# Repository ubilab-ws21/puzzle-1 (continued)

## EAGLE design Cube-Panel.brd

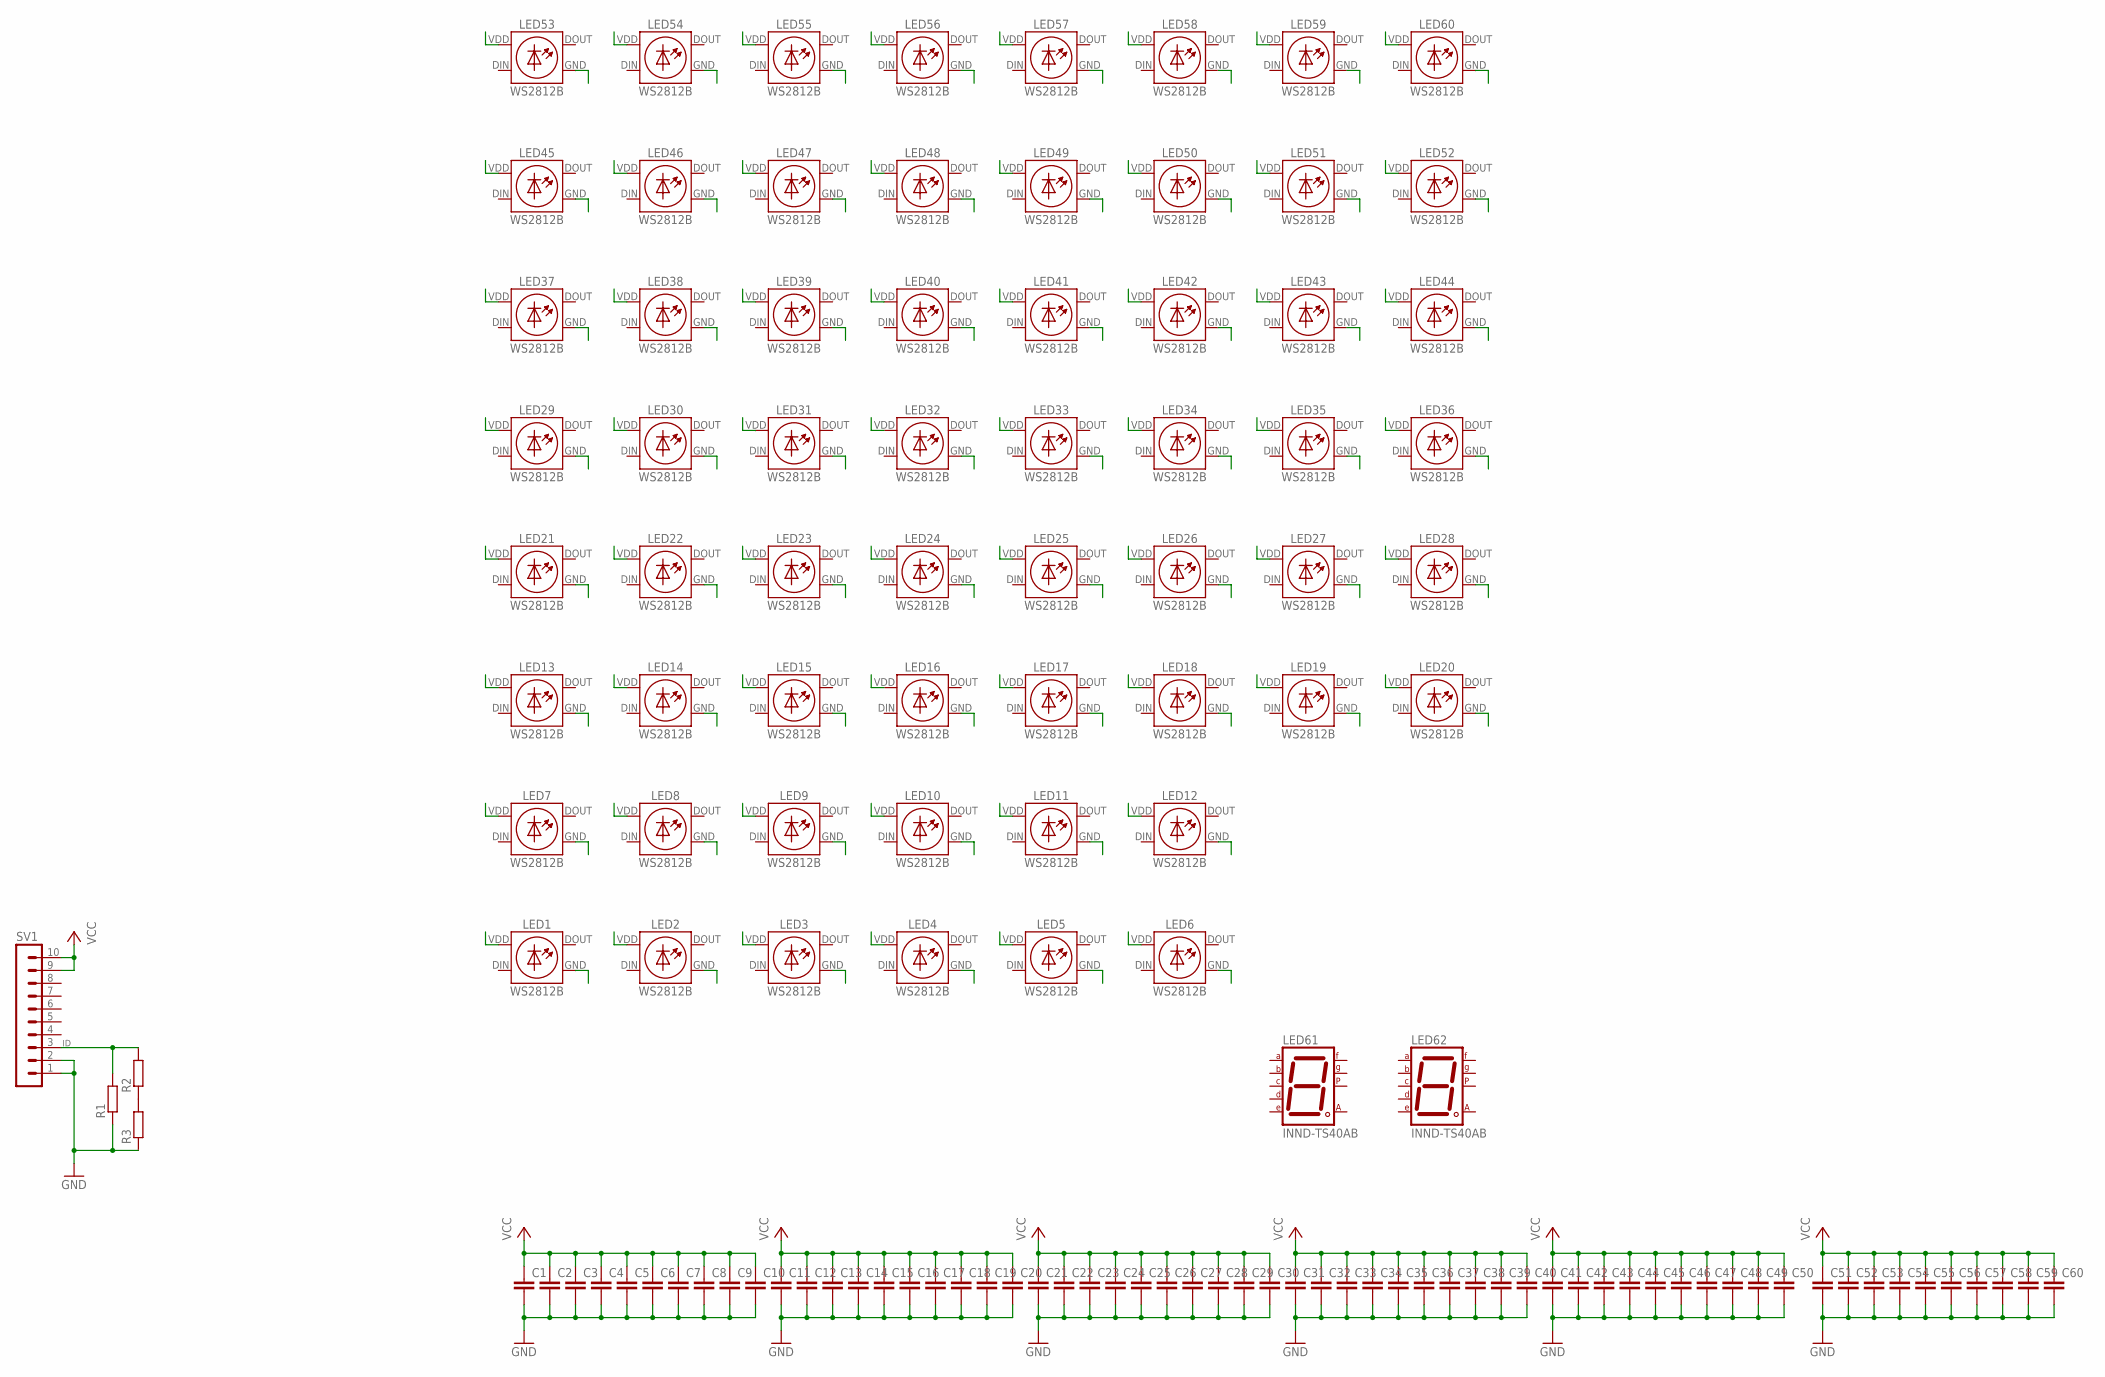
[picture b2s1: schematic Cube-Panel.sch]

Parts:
C1, C2, C3, C4, C5, C6, C7, C8, C9, C10, C11, C12, C13, C14, C15, C16, C17, C18, C19, C20, C21, C22, C23, C24, C25, C26, C27, C28, C29, C30, C31, C32, C33, C34, C35, C36, C37, C38, C39, C40, C41, C42, C43, C44, C45, C46, C47, C48, C49, C50, C51, C52, C53, C54, C55, C56, C57, C58, C59, C60: KONDENSATOR-0603; 0603
LED1, LED2, LED3, LED4, LED5, LED6, LED7, LED8, LED9, LED10, LED11, LED12, LED13, LED14, LED15, LED16, LED17, LED18, LED19, LED20, LED21, LED22, LED23, LED24, LED25, LED26, LED27, LED28, LED29, LED30, LED31, LED32, LED33, LED34, LED35, LED36, LED37, LED38, LED39, LED40, LED41, LED42, LED43, LED44, LED45, LED46, LED47, LED48, LED49, LED50, LED51, LED52, LED53, LED54, LED55, LED56, LED57, LED58, LED59, LED60: WS2812B
LED61, LED62: INND-TS40AB; 7SEG-13
R1, R2, R3: WIDERSTAND_0603; R0603
SV1: MA10-1

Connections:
GND: C1.P$2 (2), C2.P$2 (2), C3.P$2 (2), C4.P$2 (2), C5.P$2 (2), C6.P$2 (2), C7.P$2 (2), C8.P$2 (2), C9.P$2 (2), C10.P$2 (2), C11.P$2 (2), C12.P$2 (2), C13.P$2 (2), C14.P$2 (2), C15.P$2 (2), C16.P$2 (2), C17.P$2 (2), C18.P$2 (2), C19.P$2 (2), C20.P$2 (2), C21.P$2 (2), C22.P$2 (2), C23.P$2 (2), C24.P$2 (2), C25.P$2 (2), C26.P$2 (2), C27.P$2 (2), C28.P$2 (2), C29.P$2 (2), C30.P$2 (2), C31.P$2 (2), C32.P$2 (2), C33.P$2 (2), C34.P$2 (2), C35.P$2 (2), C36.P$2 (2), C37.P$2 (2), C38.P$2 (2), C39.P$2 (2), C40.P$2 (2), C41.P$2 (2), C42.P$2 (2), C43.P$2 (2), C44.P$2 (2), C45.P$2 (2), C46.P$2 (2), C47.P$2 (2), C48.P$2 (2), C49.P$2 (2), C50.P$2 (2), C51.P$2 (2), C52.P$2 (2), C53.P$2 (2), C54.P$2 (2), C55.P$2 (2), C56.P$2 (2), C57.P$2 (2), C58.P$2 (2), C59.P$2 (2), C60.P$2 (2), LED1.GND, LED2.GND, LED3.GND, LED4.GND, LED5.GND, LED6.GND, LED7.GND, LED8.GND, LED9.GND, LED10.GND, LED11.GND, LED12.GND, LED13.GND, LED14.GND, LED15.GND, LED16.GND, LED17.GND, LED18.GND, LED19.GND, LED20.GND, LED21.GND, LED22.GND, LED23.GND, LED24.GND, LED25.GND, LED26.GND, LED27.GND, LED28.GND, LED29.GND, LED30.GND, LED31.GND, LED32.GND, LED33.GND, LED34.GND, LED35.GND, LED36.GND, LED37.GND, LED38.GND, LED39.GND, LED40.GND, LED41.GND, LED42.GND, LED43.GND, LED44.GND, LED45.GND, LED46.GND, LED47.GND, LED48.GND, LED49.GND, LED50.GND, LED51.GND, LED52.GND, LED53.GND, LED54.GND, LED55.GND, LED56.GND, LED57.GND, LED58.GND, LED59.GND, LED60.GND, R1.1, R3.1, SV1.1, SV1.2
ID: R1.2, R2.2, SV1.3
unnamed: R2.1, R3.2
VCC: C1.P$1 (1), C2.P$1 (1), C3.P$1 (1), C4.P$1 (1), C5.P$1 (1), C6.P$1 (1), C7.P$1 (1), C8.P$1 (1), C9.P$1 (1), C10.P$1 (1), C11.P$1 (1), C12.P$1 (1), C13.P$1 (1), C14.P$1 (1), C15.P$1 (1), C16.P$1 (1), C17.P$1 (1), C18.P$1 (1), C19.P$1 (1), C20.P$1 (1), C21.P$1 (1), C22.P$1 (1), C23.P$1 (1), C24.P$1 (1), C25.P$1 (1), C26.P$1 (1), C27.P$1 (1), C28.P$1 (1), C29.P$1 (1), C30.P$1 (1), C31.P$1 (1), C32.P$1 (1), C33.P$1 (1), C34.P$1 (1), C35.P$1 (1), C36.P$1 (1), C37.P$1 (1), C38.P$1 (1), C39.P$1 (1), C40.P$1 (1), C41.P$1 (1), C42.P$1 (1), C43.P$1 (1), C44.P$1 (1), C45.P$1 (1), C46.P$1 (1), C47.P$1 (1), C48.P$1 (1), C49.P$1 (1), C50.P$1 (1), C51.P$1 (1), C52.P$1 (1), C53.P$1 (1), C54.P$1 (1), C55.P$1 (1), C56.P$1 (1), C57.P$1 (1), C58.P$1 (1), C59.P$1 (1), C60.P$1 (1), LED1.VDD (VCC), LED2.VDD (VCC), LED3.VDD (VCC), LED4.VDD (VCC), LED5.VDD (VCC), LED6.VDD (VCC), LED7.VDD (VCC), LED8.VDD (VCC), LED9.VDD (VCC), LED10.VDD (VCC), LED11.VDD (VCC), LED12.VDD (VCC), LED13.VDD (VCC), LED14.VDD (VCC), LED15.VDD (VCC), LED16.VDD (VCC), LED17.VDD (VCC), LED18.VDD (VCC), LED19.VDD (VCC), LED20.VDD (VCC), LED21.VDD (VCC), LED22.VDD (VCC), LED23.VDD (VCC), LED24.VDD (VCC), LED25.VDD (VCC), LED26.VDD (VCC), LED27.VDD (VCC), LED28.VDD (VCC), LED29.VDD (VCC), LED30.VDD (VCC), LED31.VDD (VCC), LED32.VDD (VCC), LED33.VDD (VCC), LED34.VDD (VCC), LED35.VDD (VCC), LED36.VDD (VCC), LED37.VDD (VCC), LED38.VDD (VCC), LED39.VDD (VCC), LED40.VDD (VCC), LED41.VDD (VCC), LED42.VDD (VCC), LED43.VDD (VCC), LED44.VDD (VCC), LED45.VDD (VCC), LED46.VDD (VCC), LED47.VDD (VCC), LED48.VDD (VCC), LED49.VDD (VCC), LED50.VDD (VCC), LED51.VDD (VCC), LED52.VDD (VCC), LED53.VDD (VCC), LED54.VDD (VCC), LED55.VDD (VCC), LED56.VDD (VCC), LED57.VDD (VCC), LED58.VDD (VCC), LED59.VDD (VCC), LED60.VDD (VCC), SV1.9, SV1.10

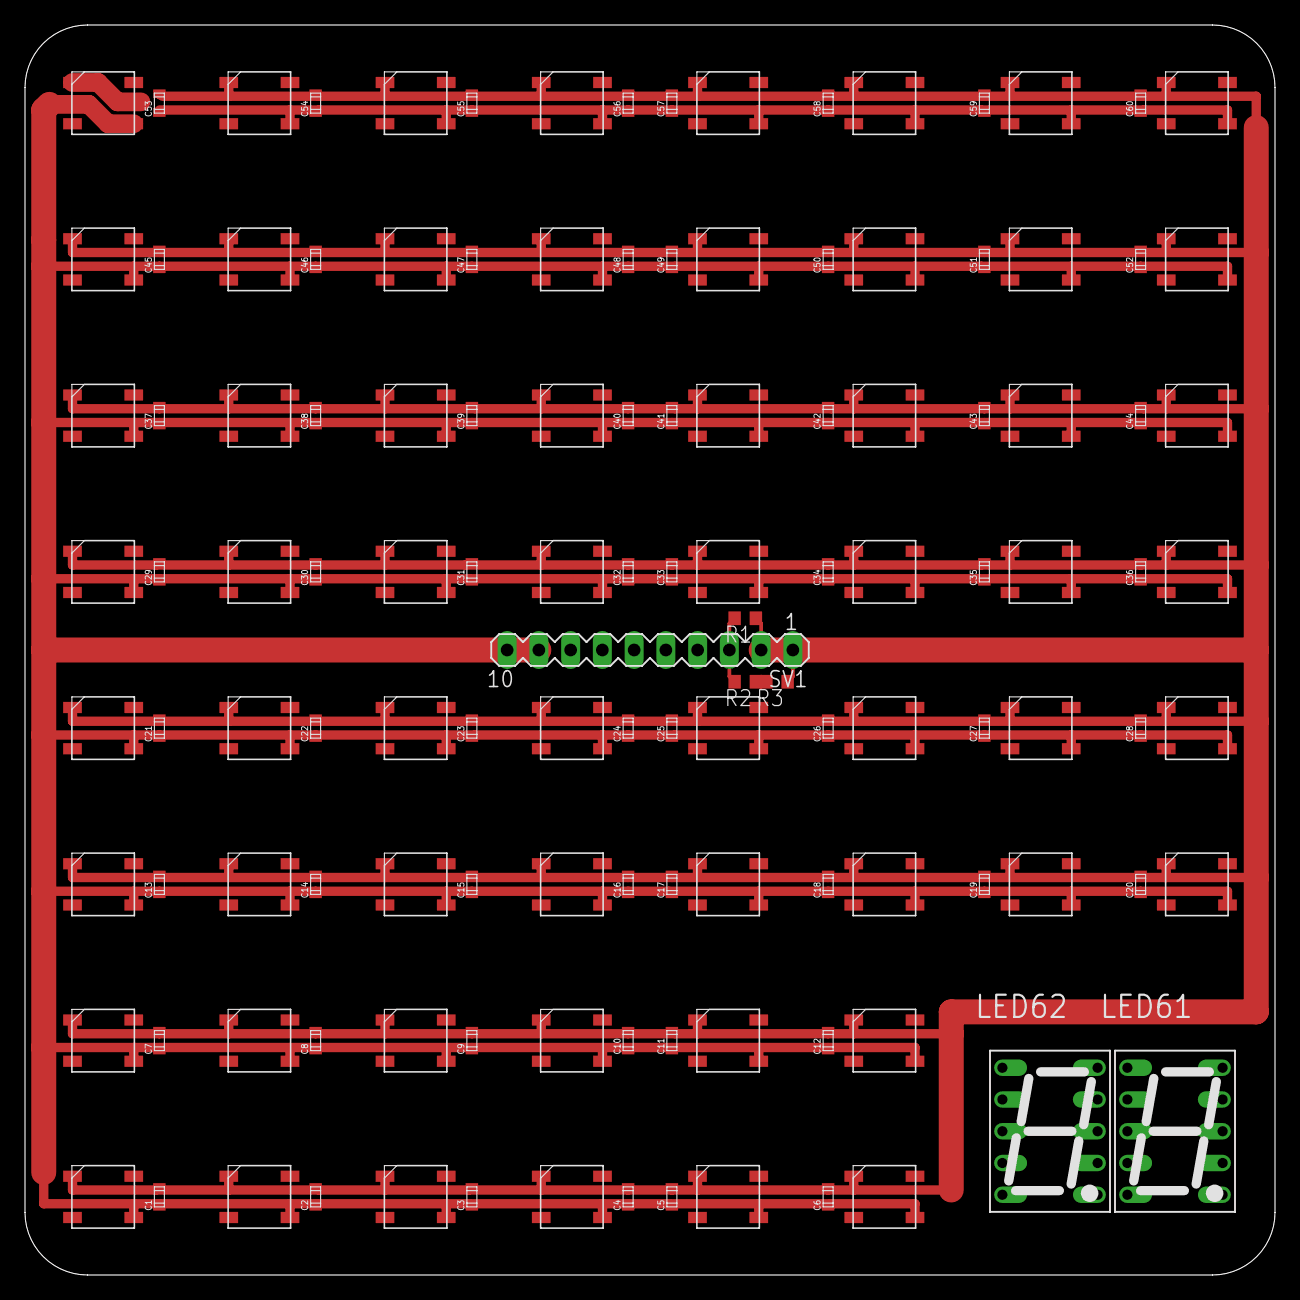
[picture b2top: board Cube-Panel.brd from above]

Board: 2 copper layers, 100.0 x 100.0 mm, 126 parts (0 on the bottom side), 4 nets.

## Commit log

2021-11-08 first attempt of meeting protocol in md.
2021-11-08 Retry of protocol in md.
2021-11-08 Added protocol of meeting from 2021-11-07.
2021-11-08 Deleted redundant file.
2021-11-08 Modified readme for first impression of puzzle.
2021-11-11 Added presentation from 11.11.21 at esclab.
2021-11-26 Cube-Panel base-design with 7-segment-display and leds.
2021-11-26 Rerouted power-traces for LEDs so the with increased from 0.75mm to 1.5mm
2021-11-28 Added Alinas concepts for the cube and the wiring task.
2021-11-28 Added concept-drawings to the readme.
2021-11-28 resized images in readme.
2021-11-28 really (?) resized images in readme.
2021-11-28 really (??) resized images in readme.
2021-11-28 Modified readme and images.
2021-11-28 Moved layout into directory.
2021-11-28 Added Attiny861 and MBI5041 for the 7-segment displays.
2021-11-28 Removed auto-backup files from eagle.
2021-11-28 Added resistors (0603) for path-configurability.
2021-11-28 Added wired data-path resistors.
2021-11-29 Added some labels and did some minor aesthetic corrections.
2021-12-02 Added Select-Resistor for LED#1
2021-12-03 Added Feedback-Trace for LED-Data. µC can now drive the LEDs. Added Single-Wire-UART-Bus for Communication.
2021-12-03 µC can now measure its own ID.
2021-12-07 Added MQTT test program
2021-12-08 Layout finalized, hopefully.
2021-12-09 Edded first design of a side-panel to be mounted on the PCB for good looks.
2021-12-09 Added first demo of the clue-sheet for the movement-sequence.
2021-12-09 Added initial version of clue-sheet.
2021-12-09 Minor cleanup.
2021-12-09 Modified MQTT_Test file
2021-12-13 orientation detection script added
    probably still contains a bug, as one of the sensors is not detected properly and the other one is giving strange results
2021-12-16 Delete Orientation_script.ino
    this script has been complete changed and therefore it is getting deletet and the new one uploaded
2021-12-16 the new orientation and code checking script
2022-01-27 Updated MQTT file
2022-01-28 Added Models for basic mechanical construction of the cube.
2022-01-28 Create MQTT_Topics
2022-01-28 Update MQTT_Topics
2022-02-03 Sample code to test IMU+LEDs
2022-02-03 Updated MQTT_Topics
2022-02-03 Updated CubePuzzle.h
2022-02-03 Updated MQTT.ino
2022-02-04 merging of code detection and LED feedback
    unfortnately i didn't clone the repository, but copied the code, which is why i can't commit it but have to reupload it...
2022-02-04 Modified CubePuzzle.h
2022-02-04 Modified MQTT.ino
2022-02-08 Updated Cube.ino
2022-02-09 Current version of the wall firmware.
2022-02-09 Merging of orientation detection, LED and MQTT
2022-02-09 Header File for MQTT Merged
2022-02-09 Wall works.
2022-02-10 Added delays so we do not spam the bus.
2022-02-10 Header File for Wall
2022-02-10 final code for the cube
2022-02-10 final code for the cube header
2022-02-10 final code for the panel
2022-02-10 final code for the panel header file
2022-02-10 MQTT is now using the right communication format
2022-02-10 Added file suffixes.
2022-02-10 Moved port of KBUS on Wall.
2022-02-10 Changed includes to be complient with Google style syntax.
2022-02-10 Moving around stuff.
2022-02-11 Corrected KBUS-Pins, Lowered brightness when solved, slowed activation of displays for pin.
2022-02-28 Added all Sidepanel-Prints + Diffusors.
2022-03-03 Reduced with for LED-Cover P0 (test) for assembly.
2022-03-03 Reduced outline by 0.1mm instead of 1.0
2022-03-03 Added Prints for symbols (dual extrusion!!)
2022-03-03 Width reduction for p4.
2022-03-03 undo width reduction ...
2022-03-03 Undone width reduction.
2022-03-03 Redesign of panel6 for better printability.
2022-03-04 fixing an mqtt bug
2022-03-04 mqtt bug fix
2022-03-09 Improved panel communication.
2023-04-16 changed order of MQTT-Messages, since the order of sending sometimes caused issues, I guess
